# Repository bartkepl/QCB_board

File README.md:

# QCB (Quad Card Backplane)

Quad Card Backplane for 3U eurocards. Splits USB 2.0 and 10/100M Ethernet (plus RS485 and an ID EEPROM) out to 4 eurocards.

---

## Status: ready for prototype order

- Schematic and PCB routing are done (rev 0.1), production files generated.
- A full design review (schematic + PCB + EMC + SPICE) was completed on 2026-08-03 and re-checked since; see [Documentation](#documentation) below.
- Fiducials added (2 per side, hand assembly), Y2 load caps C41/C42 now included in the BOM, datasheets for IP175G, FE1.1s and UT8413A in [doc/datasheet/](doc/datasheet/).

Production outputs: [schematic PDF](prod/sch/QCB_board.pdf) · [PCB PDF](prod/pcb/QCB_board.pdf) · [interactive BOM](prod/ibom/QCB_board_ibom.html) · [gerbers](prod/QCB_board.zip)

---

## Architecture

The board is a backplane hub card built around two switching ICs, fanned out to 4 identical eurocard channels:

- **U1 (FE1.1s)** — 4-port USB 2.0 Hi-Speed hub, one port per channel.
- **IC1 (IP175G)** — 5-port 10/100 Ethernet switch. One port is broken out to an RJ45 (J3) via magnetics (H1102NL); the other 4 go to the channels.
- **4× channel (`con1.kicad_sch`, reused as CON1–CON4)** — each with its own USB D+/D-, Ethernet TX/RX pairs, RS485±, ESD protection, and an identification EEPROM (M24C02) on its own I2C bus.
- **`pwr.kicad_sch`** — power input (Molex Mini-Fit connector J6), polyfuse, ferrite bead, ESD protection. No on-board regulator — +3.3V/+5V/+12V are supplied by the backplane.
- Channels land on 4 backplane connectors (DIN41612 2×32, J7–J10).

4-layer PCB (F.Cu / In1.Cu / In2.Cu / B.Cu), 101.6 × 128.7 mm.

## Features

- 10/100 Ethernet switch with an external RJ45 port
- USB 2.0 Hi-Speed 4-port hub
- Per-channel RS485 and identification EEPROM
- 4× 3U 6TE eurocard, IEEE 1101.1-1998 format (128 × 30.1 mm)
- Powered entirely from the backplane (no on-board regulator)

## Repository structure

```
pcb/        KiCad project (schematic, PCB, jobsets, 3D packages, datasheets cache)
doc/        Design review report, TODO list and component datasheets (tracked, human-readable)
media/      Renders/photos used in this README
prod/       Generated production outputs (gerbers/zip, BOM, schematic & PCB PDFs)
analysis/   Raw output of automated design-review tooling (gitignored, regenerable)
```

## Documentation

- [doc/DESIGN_REVIEW_2026-08-03.md](doc/DESIGN_REVIEW_2026-08-03.md) — full schematic/PCB/EMC/SPICE design review
- [doc/TODO.md](doc/TODO.md) — outstanding items before the board can be ordered

## License and Contribution

[MIT License](/LICENSE)

Open to contributions in both software and hardware!

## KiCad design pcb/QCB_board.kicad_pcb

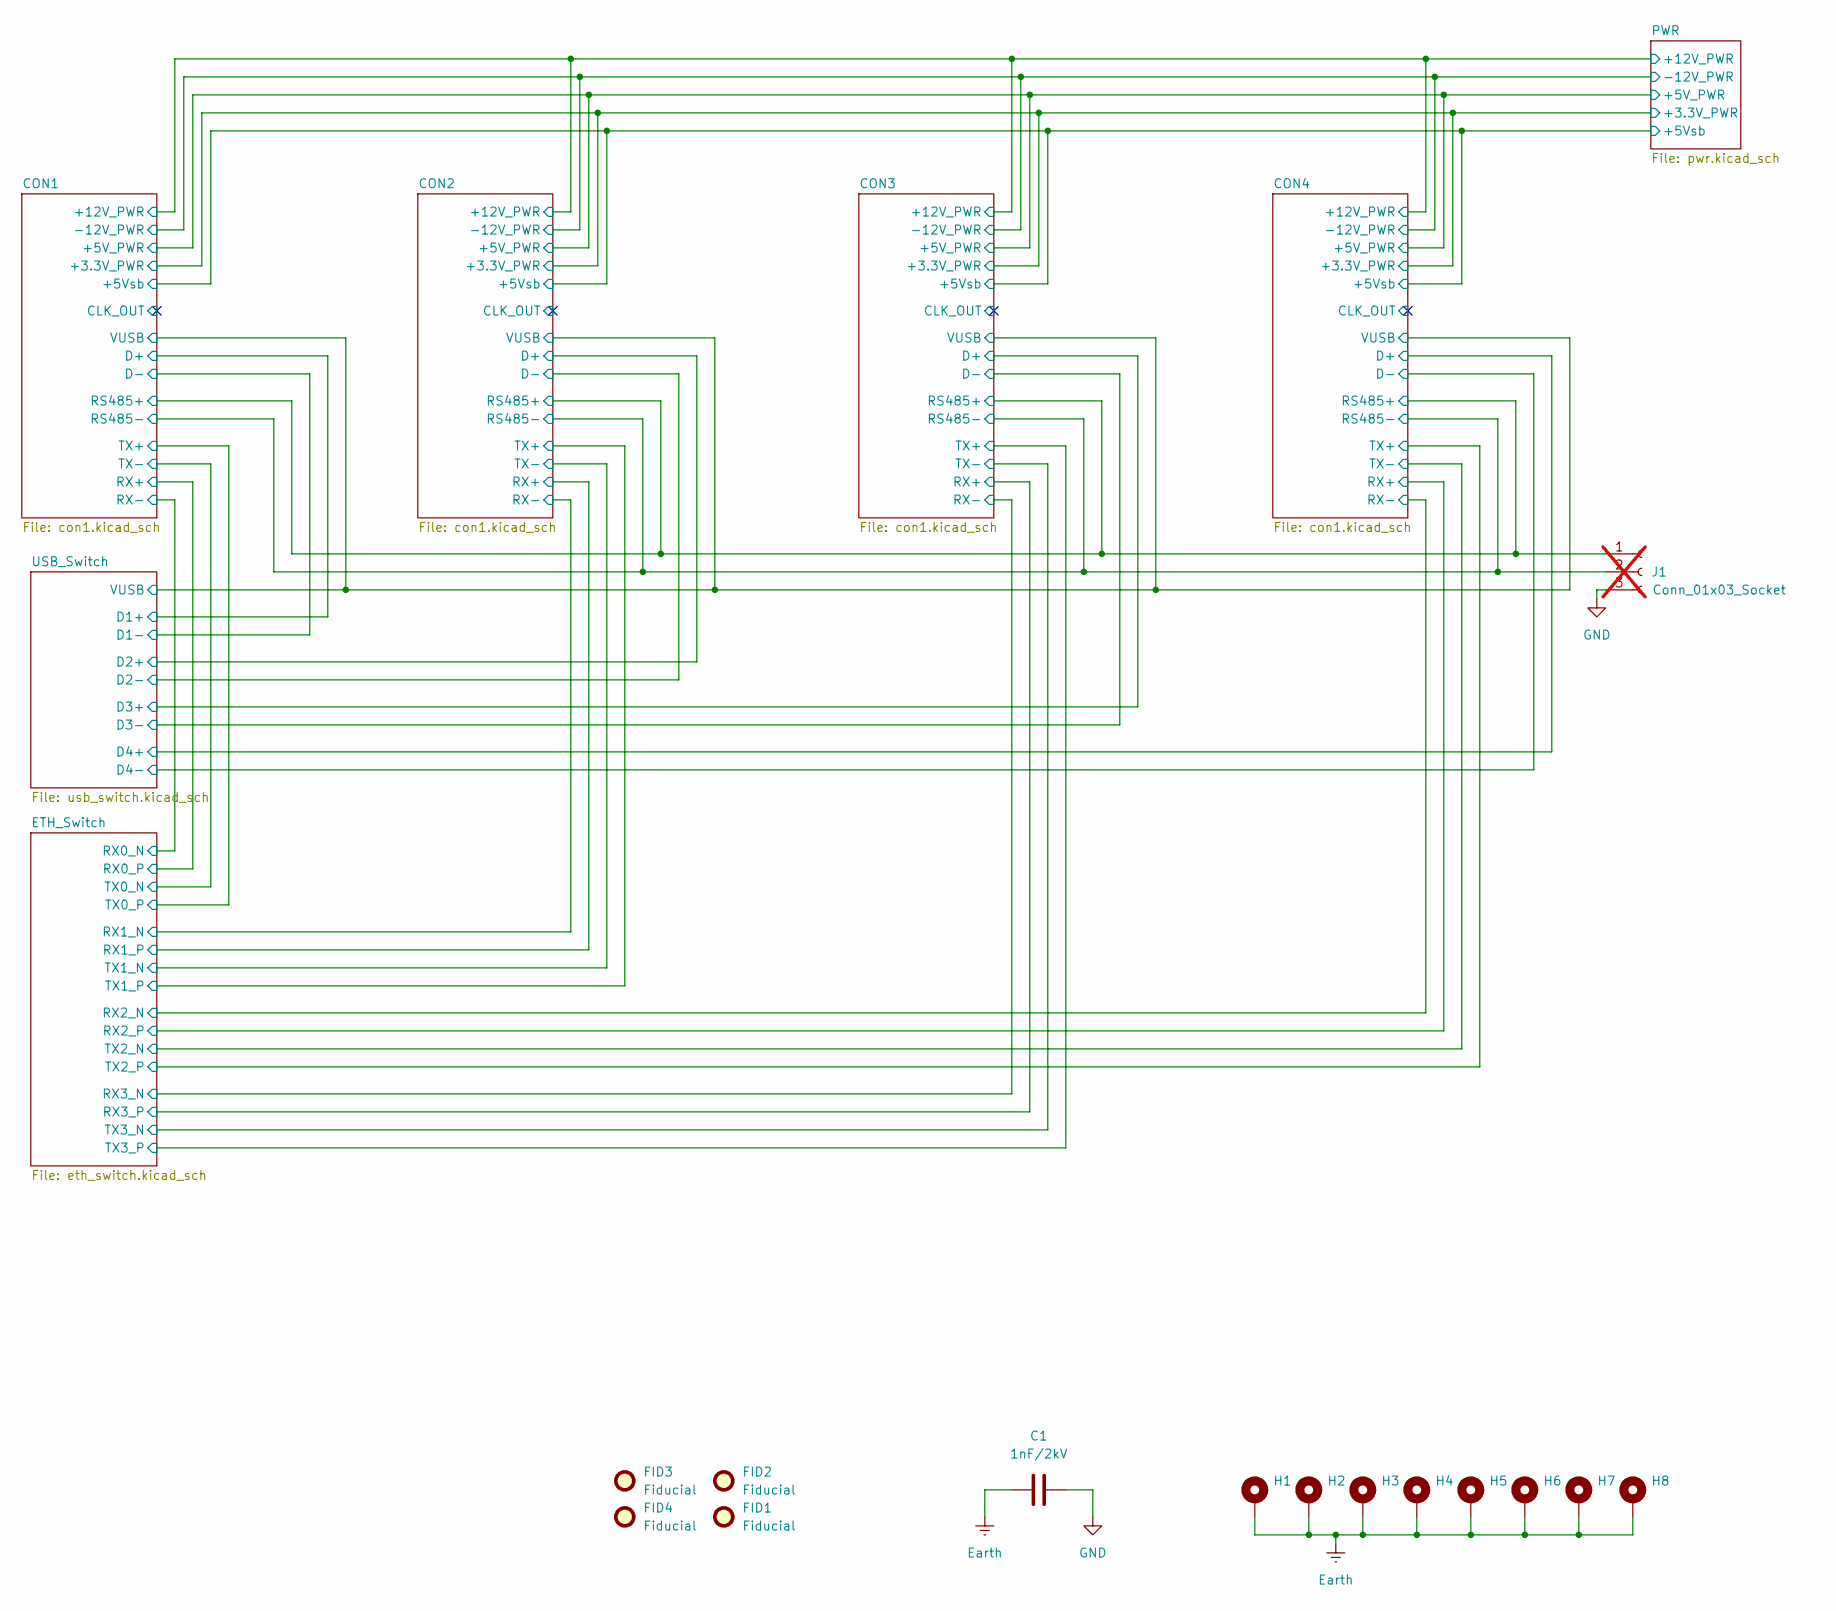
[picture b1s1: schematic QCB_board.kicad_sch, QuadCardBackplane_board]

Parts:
C1: 1nF/2kV; C_1206_3216Metric; MPN C1206X102K202T; LCSC C106012
FID1, FID2, FID3, FID4: Fiducial; Fiducial_0.5mm_Mask1mm
H1, H2, H3, H4, H5, H6, H7, H8: MountingHole_Pad; MountingHole_2.7mm_M2.5_DIN965_Pad
J1: Conn_01x03_Socket; JST_PH_B3B-PH-K_1x03_P2.00mm_Vertical; not fitted

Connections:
/CON1/RS485+: J1.1; also elsewhere on the board
/CON1/RS485-: J1.2; also elsewhere on the board
Earth: C1.1, H1.1 (1_1), H2.1 (1_1), H3.1 (1_1), H4.1 (1_1), H5.1 (1_1), H6.1 (1_1), H7.1 (1_1), H8.1 (1_1); also elsewhere on the board
GND: C1.2, J1.3; also elsewhere on the board

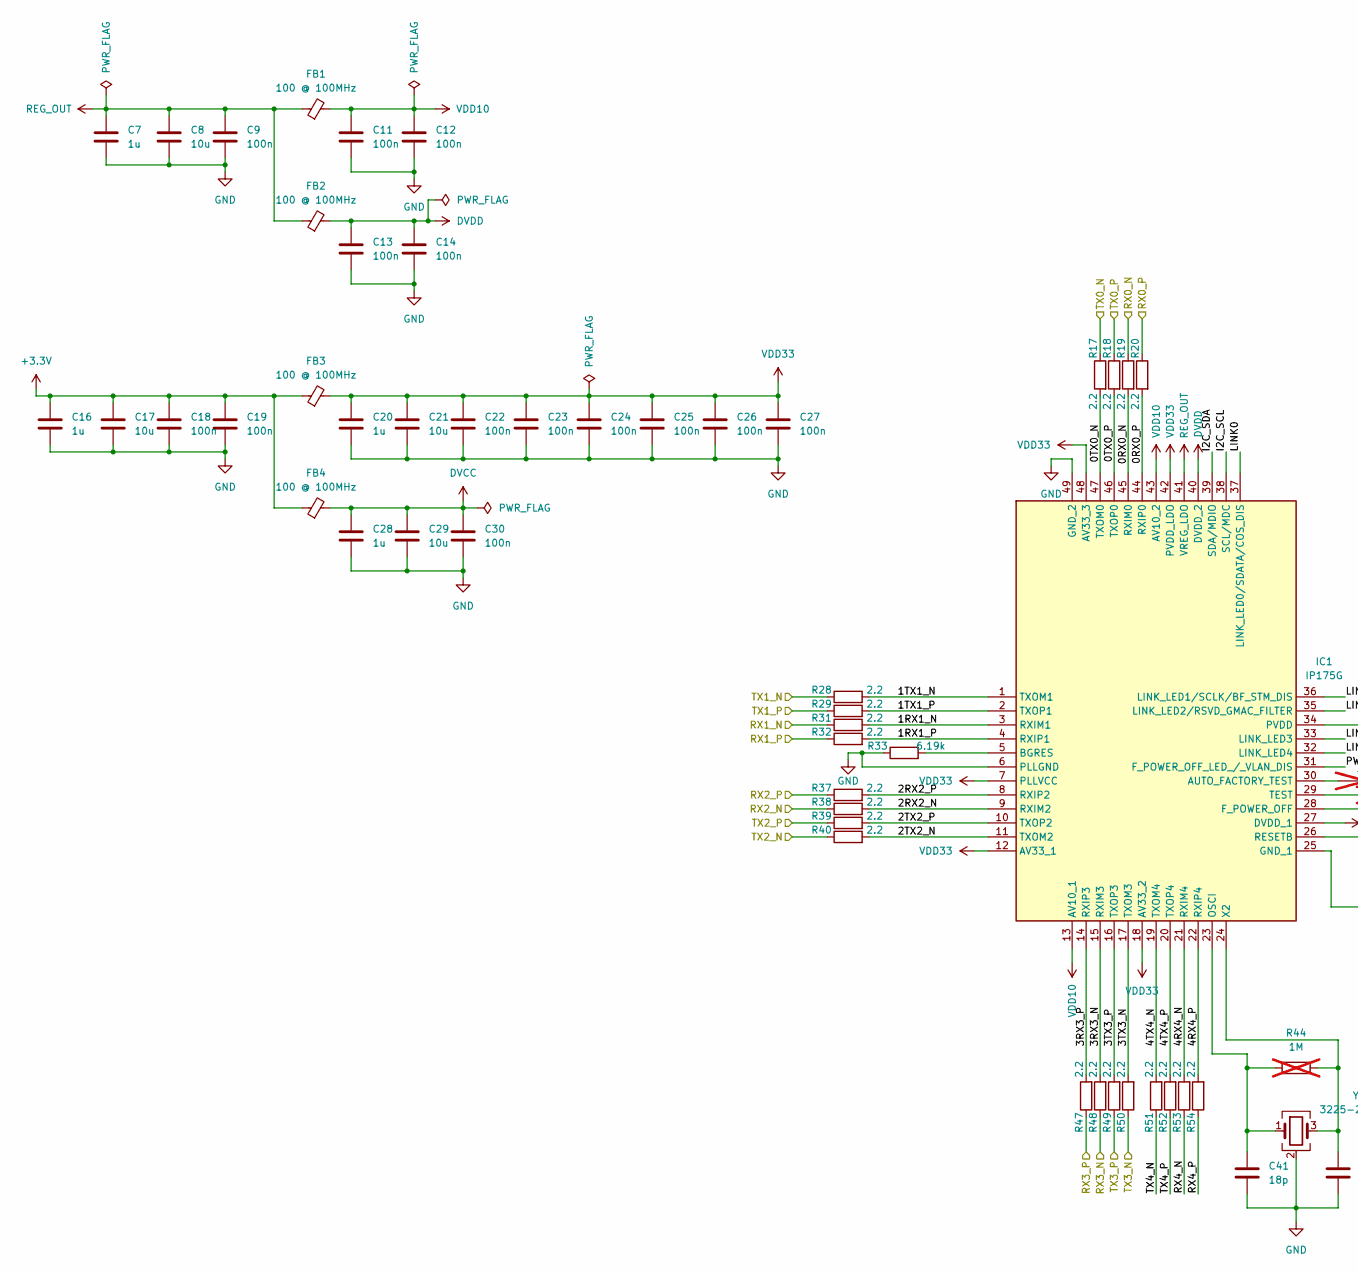
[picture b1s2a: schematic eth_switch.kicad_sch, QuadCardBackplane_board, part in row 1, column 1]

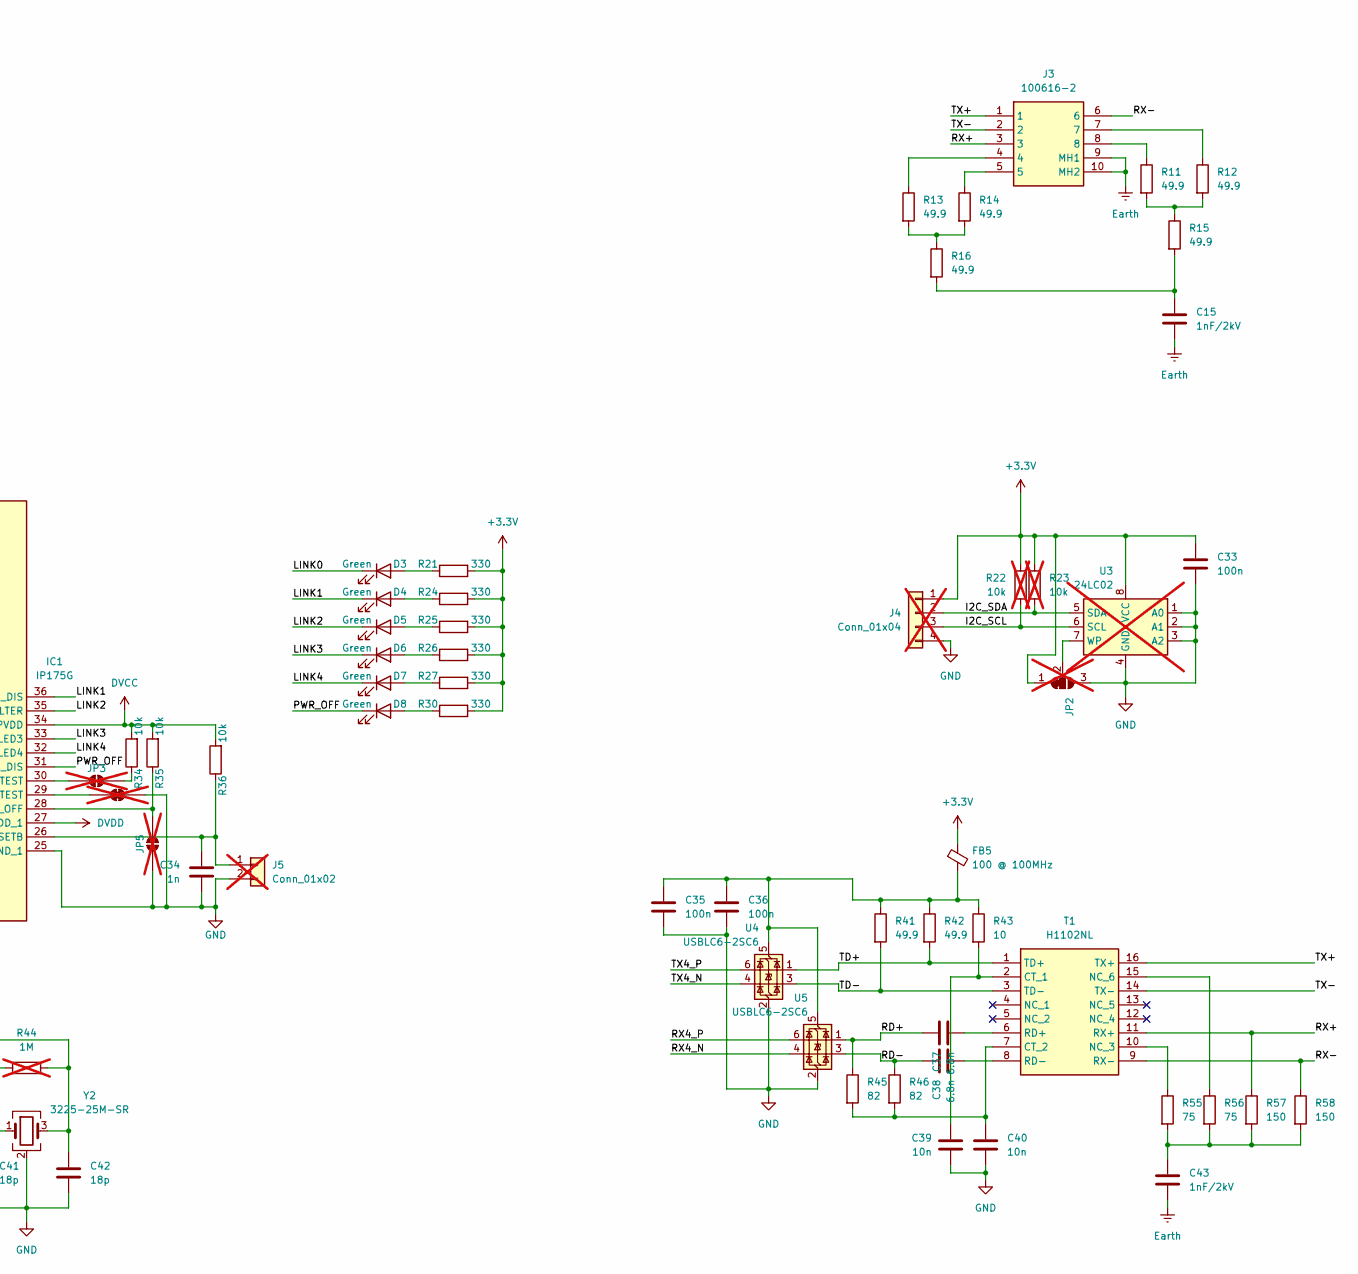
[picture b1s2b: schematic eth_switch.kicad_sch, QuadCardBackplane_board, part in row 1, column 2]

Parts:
C7, C16, C20, C28: 1u; C_0603_1608Metric; MPN 0603X105K500NT; LCSC C157684
C8, C17, C21, C29: 10u; C_1206_3216Metric; MPN CS3216X5R106K500NRI; LCSC C513774
C9, C11, C12, C13, C14, C18, C19, C22, C23, C24, C25, C26, C27, C30, C33, C35, C36: 100n; C_0603_1608Metric; MPN TCC0603X7R104K500CT; LCSC C282519
C15, C43: 1nF/2kV; C_1206_3216Metric; MPN C1206X102K202T; LCSC C106012
C34: 1n; C_0603_1608Metric; MPN CC0603JRNPO9BN102; LCSC C106246
C37, C38: 6.8n; C_0603_1608Metric; MPN C1608C0G1H682JT000N; LCSC C342851
C39, C40: 10n; C_0603_1608Metric; MPN GRM1885C1H103JA01J; LCSC C2215227
C41, C42: 18p; C_0402_1005Metric; MPN 0402CG180J500NT; LCSC C1549
D3, D4, D5, D6, D7, D8: Green; LED_0603_1608Metric; MPN N0G69S04
FB1, FB2, FB3, FB4, FB5: 100 @ 100MHz; L_0603_1608Metric_Pad1.05x0.95mm_HandSolder; MPN MH1608-101Y
IC1: IP175G; QFN40P600X600X90-49N-D; MPN IP175G; LCSC C80220
J3: 100616-2; 1006162; MPN 100616-2
J4: Conn_01x04; PinHeader_1x04_P1.00mm_Vertical; not fitted
J5: Conn_01x02; PinHeader_1x02_P1.00mm_Vertical; not fitted
JP2: SolderJumper_3_Bridged12; SolderJumper-3_P1.3mm_Bridged12_Pad1.0x1.5mm; not fitted
JP3, JP5: SolderJumper_2_Open; SolderJumper-2_P1.3mm_Open_RoundedPad1.0x1.5mm; not fitted
JP4: SolderJumper_2_Bridged; SolderJumper-2_P1.3mm_Bridged_RoundedPad1.0x1.5mm; not fitted
R11, R12, R13, R14, R15, R16, R41, R42: 49.9; R_0603_1608Metric; MPN SCR0603F49R9; LCSC C3016250
R17, R18, R19, R20, R28, R29, R31, R32, R37, R38, R39, R40, R47, R48, R49, R50, R51, R52, R53, R54: 2.2; R_0603_1608Metric; MPN FRC0603F2R20TS; LCSC C2907006
R21, R24, R25, R26, R27, R30: 330; R_0603_1608Metric; MPN SCR0603F330R; LCSC C3016255
R22, R23: 10k; R_0603_1608Metric; not fitted
R33: 6.19k; R_0603_1608Metric; MPN 0603WAF6191T5E; LCSC C25978
R34, R35, R36: 10k; R_0603_1608Metric; MPN RMS06FT1002; LCSC C209013
R43: 10; R_0603_1608Metric; MPN 0603WAF100JT5E; LCSC C22859
R44: 1M; R_0603_1608Metric; MPN 0603SAF1004T5E; not fitted
R45, R46: 82; R_0603_1608Metric; MPN FRC0603F82R0TS; LCSC C2907073
R55, R56: 75; R_0603_1608Metric; MPN 0603WAF750JT5E; LCSC C4275
R57, R58: 150; R_0603_1608Metric; MPN 0603WAF1500T5E; LCSC C22808
T1: H1102NL; SOIC127P940X597-16N; MPN H1102NLT; LCSC C20623173
U3: 24LC02; SOIC-8_3.9x4.9mm_P1.27mm; not fitted
U4, U5: USBLC6-2SC6; SOT-23-6_Handsoldering; MPN USBLC6-2SC6; LCSC C7519
Y2: 3225-25M-SR; Crystal_SMD_3225-4Pin_3.2x2.5mm; MPN 3225-25M-SR

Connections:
+3.3V: C16.1, C17.1, C18.1, C19.1, C33.1, FB3.1, FB4.1, FB5.1, J4.1, JP2.1 (A), R21.2, R22.2, R23.2, R24.2, R25.2, R26.2, R27.2, R30.2, U3.8 (VCC); also elsewhere on the board
/CON1/RX+: R20.1; also elsewhere on the board
/CON1/RX-: R19.1; also elsewhere on the board
/CON1/TX+: R18.1; also elsewhere on the board
/CON1/TX-: R17.1; also elsewhere on the board
/CON2/RX+: R32.1; also elsewhere on the board
/CON2/RX-: R31.1; also elsewhere on the board
/CON2/TX+: R29.1; also elsewhere on the board
/CON2/TX-: R28.1; also elsewhere on the board
/CON3/RX+: R47.1; also elsewhere on the board
/CON3/RX-: R48.1; also elsewhere on the board
/CON3/TX+: R49.1; also elsewhere on the board
/CON3/TX-: R50.1; also elsewhere on the board
/CON4/RX+: R37.1; also elsewhere on the board
/CON4/RX-: R38.1; also elsewhere on the board
/CON4/TX+: R39.1; also elsewhere on the board
/CON4/TX-: R40.1; also elsewhere on the board
/ETH_Switch/0RX0_N: IC1.45 (RXIM0), R19.2
/ETH_Switch/0RX0_P: IC1.44 (RXIP0), R20.2
/ETH_Switch/0TX0_N: IC1.47 (TXOM0), R17.2
/ETH_Switch/0TX0_P: IC1.46 (TXOP0), R18.2
/ETH_Switch/1RX1_N: IC1.3 (RXIM1), R31.2
/ETH_Switch/1RX1_P: IC1.4 (RXIP1), R32.2
/ETH_Switch/1TX1_N: IC1.1 (TXOM1), R28.2
/ETH_Switch/1TX1_P: IC1.2 (TXOP1), R29.2
/ETH_Switch/2RX2_N: IC1.9 (RXIM2), R38.2
/ETH_Switch/2RX2_P: IC1.8 (RXIP2), R37.2
/ETH_Switch/2TX2_N: IC1.11 (TXOM2), R40.2
/ETH_Switch/2TX2_P: IC1.10 (TXOP2), R39.2
/ETH_Switch/3RX3_N: IC1.15 (RXIM3), R48.2
/ETH_Switch/3RX3_P: IC1.14 (RXIP3), R47.2
/ETH_Switch/3TX3_N: IC1.17 (TXOM3), R50.2
/ETH_Switch/3TX3_P: IC1.16 (TXOP3), R49.2
/ETH_Switch/4RX4_N: IC1.21 (RXIM4), R53.2
/ETH_Switch/4RX4_P: IC1.22 (RXIP4), R54.2
/ETH_Switch/4TX4_N: IC1.19 (TXOM4), R51.2
/ETH_Switch/4TX4_P: IC1.20 (TXOP4), R52.2
/ETH_Switch/I2C_SCL: IC1.38 (SCL/MDC), J4.3, R22.1, U3.6 (SCL)
/ETH_Switch/I2C_SDA: IC1.39 (SDA/MDIO), J4.2, R23.1, U3.5 (SDA)
/ETH_Switch/LINK0: D3.1 (K), IC1.37 (LINK_LED0/SDATA/COS_DIS)
/ETH_Switch/LINK1: D4.1 (K), IC1.36 (LINK_LED1/SCLK/BF_STM_DIS)
/ETH_Switch/LINK2: D5.1 (K), IC1.35 (LINK_LED2/RSVD_GMAC_FILTER)
/ETH_Switch/LINK3: D6.1 (K), IC1.33 (LINK_LED3)
/ETH_Switch/LINK4: D7.1 (K), IC1.32 (LINK_LED4)
/ETH_Switch/PWR_OFF: D8.1 (K), IC1.31 (F_POWER_OFF_LED_/_VLAN_DIS)
/ETH_Switch/RD+: C37.2, R45.1, U5.1 (I/O1)
/ETH_Switch/RD-: C38.2, R46.1, U5.3 (I/O2)
/ETH_Switch/RX4_N: R53.1, U5.4 (I/O2)
/ETH_Switch/RX4_P: R54.1, U5.6 (I/O1)
/ETH_Switch/RX+: J3.3, R57.1, T1.11 (RX+)
/ETH_Switch/RX-: J3.6, R58.1, T1.9 (RX-)
/ETH_Switch/TD+: R42.2, T1.1 (TD+), U4.1 (I/O1)
/ETH_Switch/TD-: R41.2, T1.3 (TD-), U4.3 (I/O2)
/ETH_Switch/TX4_N: R51.1, U4.4 (I/O2)
/ETH_Switch/TX4_P: R52.1, U4.6 (I/O1)
/ETH_Switch/TX+: J3.1, T1.16 (TX+)
/ETH_Switch/TX-: J3.2, T1.14 (TX-)
DVCC: C28.1, C29.1, C30.1, FB4.2, IC1.34 (PVDD), R34.2, R35.2, R36.2
DVDD: C13.1, C14.1, FB2.2, IC1.27 (DVDD_1), IC1.40 (DVDD_2)
Earth: C15.2, C43.2, J3.9 (MH1), J3.10 (MH2); also elsewhere on the board
GND: C7.2, C8.2, C9.2, C11.2, C12.2, C13.2, C14.2, C16.2, C17.2, C18.2, C19.2, C20.2, C21.2, C22.2, C23.2, C24.2, C25.2, C26.2, C27.2, C28.2, C29.2, C30.2, C33.2, C34.1, C35.2, C36.2, C39.1, C40.2, C41.2, C42.2, IC1.6 (PLLGND), IC1.25 (GND_1), IC1.49 (GND_2), J4.4, J5.2, JP2.3 (B), JP4.2 (B), JP5.1 (A), R33.1, U3.1 (A0), U3.2 (A1), U3.3 (A2), U3.4 (GND), U4.2 (GND), U5.2 (GND), Y2.2 (G), Y2.4 (G); also elsewhere on the board
unnamed: C15.1, R15.2, R16.2
unnamed: C43.1, R55.2, R56.2, R57.2, R58.2
unnamed: D3.2 (A), R21.1
unnamed: D4.2 (A), R24.1
unnamed: D5.2 (A), R25.1
unnamed: D6.2 (A), R26.1
unnamed: D7.2 (A), R27.1
unnamed: D8.2 (A), R30.1
unnamed: IC1.30 (AUTO_FACTORY_TEST), JP3.1 (A)
unnamed: IC1.5 (BGRES), R33.2
unnamed: IC1.28 (F_POWER_OFF), JP5.2 (B), R35.1
unnamed: C41.1, IC1.23 (OSCI), R44.1, Y2.1
unnamed: C34.2, IC1.26 (RESETB), J5.1, R36.1
unnamed: IC1.29 (TEST), JP4.1 (A)
unnamed: C42.1, IC1.24 (X2), R44.2, Y2.3
unnamed: J3.4, R13.1
unnamed: J3.5, R14.1
unnamed: J3.7, R12.1
unnamed: J3.8, R11.1
unnamed: JP2.2 (C), U3.7 (WP)
unnamed: JP3.2 (B), R34.1
unnamed: R11.2, R12.2, R15.1
unnamed: R13.2, R14.2, R16.1
unnamed: C39.2, R43.2, T1.2 (CT_1)
unnamed: C40.1, R45.2, R46.2, T1.7 (CT_2)
unnamed: R55.1, T1.10 (NC_3)
unnamed: R56.1, T1.15 (NC_6)
unnamed: C37.1, T1.6 (RD+)
unnamed: C38.1, T1.8 (RD-)
unnamed: C35.1, C36.1, FB5.2, R41.1, R42.1, R43.1, U4.5 (VBUS), U5.5 (VBUS)
REG_OUT: C7.1, C8.1, C9.1, FB1.1, FB2.1, IC1.41 (VREG_LDO)
VDD10: C11.1, C12.1, FB1.2, IC1.13 (AV10_1), IC1.43 (AV10_2)
VDD33: C20.1, C21.1, C22.1, C23.1, C24.1, C25.1, C26.1, C27.1, FB3.2, IC1.7 (PLLVCC), IC1.12 (AV33_1), IC1.18 (AV33_2), IC1.42 (PVDD_LDO), IC1.48 (AV33_3)

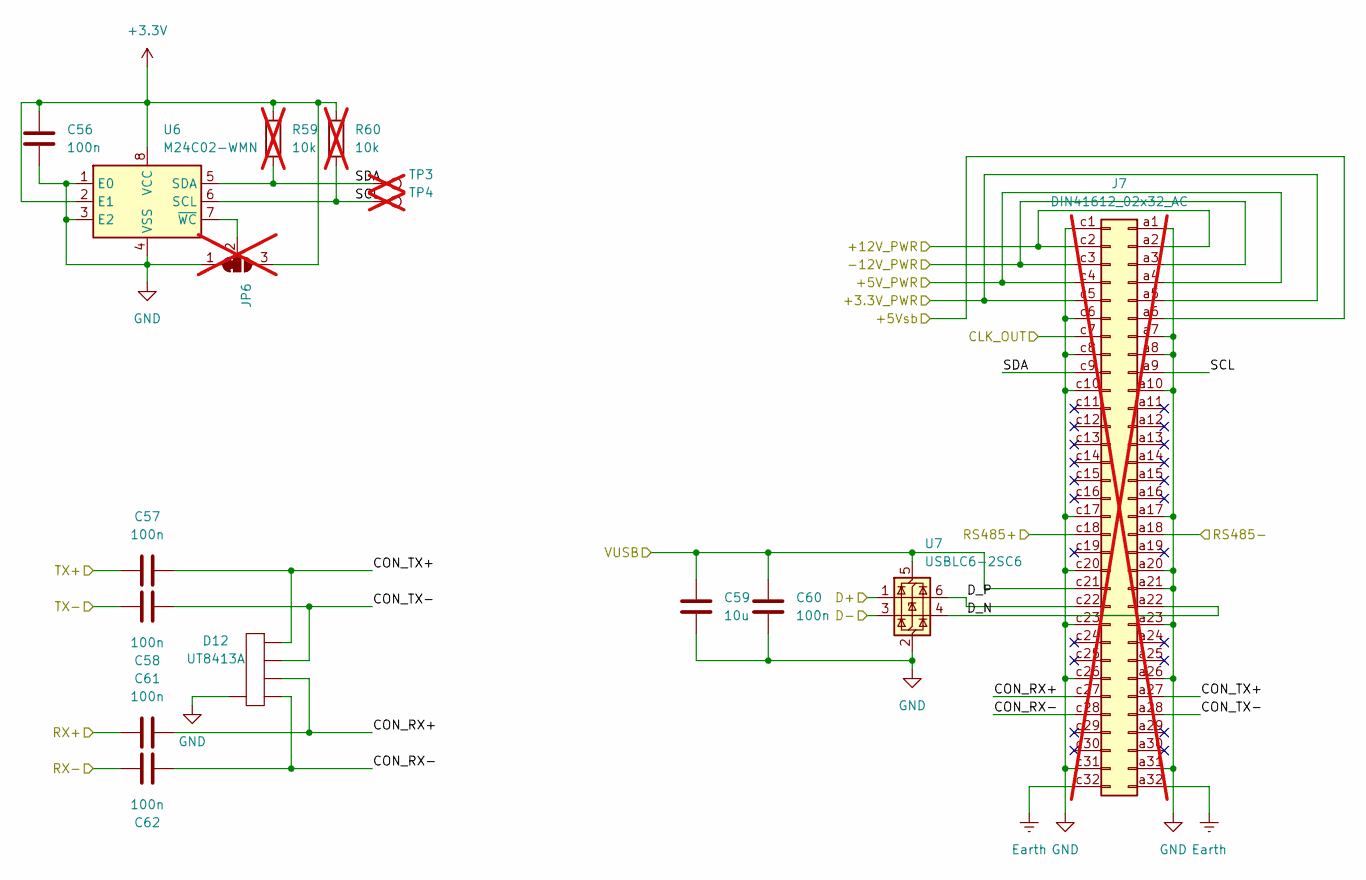
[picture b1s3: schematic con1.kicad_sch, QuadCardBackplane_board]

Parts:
C56, C60: 100n; C_0603_1608Metric; MPN TCC0603X7R104K500CT; LCSC C282519
C57, C58, C61, C62: 100n; C_0805_2012Metric; MPN C2012X7T2E104K125AA; Mouser 810-C2012X7T2E104KAA
C59: 10u; C_1206_3216Metric; MPN CS3216X5R106K500NRI; LCSC C513774
D12: UT8413A; Diodes_UDFN-10_1x2.5mm_P0.5mm; MPN UT8413A
J7: DIN41612_02x32_AC; DIN41612_C_2x32_Female_Vertical_THT; not fitted
JP6: SolderJumper_3_Bridged12; SolderJumper-3_P1.3mm_Bridged12_Pad1.0x1.5mm; not fitted
R59, R60: 10k; R_0603_1608Metric; not fitted
TP3, TP4: TestPoint; TestPoint_Pad_D1.0mm; not fitted
U6: M24C02-WMN; SOIC-8_3.9x4.9mm_P1.27mm; MPN M24C02-WMN6TP; Mouser 511-M24C02-WMN6TP
U7: USBLC6-2SC6; SOT-23-6_Handsoldering; MPN USBLC6-2SC6; LCSC C7519

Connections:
+3.3V: C56.2, JP6.3 (B), R59.2, R60.2, U6.2 (E1), U6.8 (VCC); also elsewhere on the board
/CON1/+3.3V_PWR: J7.a5, J7.c5; also elsewhere on the board
/CON1/+5V_PWR: J7.a4, J7.c4; also elsewhere on the board
/CON1/+5Vsb: J7.a6; also elsewhere on the board
/CON1/+12V_PWR: J7.a2, J7.c2; also elsewhere on the board
/CON1/-12V_PWR: J7.a3, J7.c3; also elsewhere on the board
/CON1/CLK_OUT: J7.c7
/CON1/CON_RX+: C61.2, D12.2, D12.9, J7.c27
/CON1/CON_RX-: C62.2, D12.1, D12.10, J7.c28
/CON1/CON_TX+: C57.2, D12.5, D12.6, J7.a27
/CON1/CON_TX-: C58.2, D12.4, D12.7, J7.a28
/CON1/D+: U7.1 (I/O1); also elsewhere on the board
/CON1/D-: U7.3 (I/O2); also elsewhere on the board
/CON1/D_N: J7.a22, U7.4 (I/O2)
/CON1/D_P: J7.c22, U7.6 (I/O1)
/CON1/RS485+: J7.c18; also elsewhere on the board
/CON1/RS485-: J7.a18; also elsewhere on the board
/CON1/RX+: C61.1; also elsewhere on the board
/CON1/RX-: C62.1; also elsewhere on the board
/CON1/SCL: J7.a9, R60.1, TP4.1 (1_1), U6.6 (SCL)
/CON1/SDA: J7.c9, R59.1, TP3.1 (1_1), U6.5 (SDA)
/CON1/TX+: C57.1; also elsewhere on the board
/CON1/TX-: C58.1; also elsewhere on the board
/CON1/VUSB: C59.1, C60.2, J7.c21, U7.5 (VBUS); also elsewhere on the board
Earth: J7.a32, J7.c32; also elsewhere on the board
GND: C56.1, C59.2, C60.1, D12.3, D12.8, J7.a1, J7.a7, J7.a8, J7.a10, J7.a17, J7.a20, J7.a21, J7.a23, J7.a26, J7.a31, J7.c1, J7.c6, J7.c8, J7.c10, J7.c17, J7.c20, J7.c23, J7.c26, J7.c31, JP6.1 (A), U6.1 (E0), U6.3 (E2), U6.4 (VSS), U7.2 (GND); also elsewhere on the board
unnamed: JP6.2 (C), U6.7 (~WC)

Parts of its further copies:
C63, C67, C70, C74, C77, C81: 100n; C_0603_1608Metric; MPN TCC0603X7R104K500CT; LCSC C282519
C64, C65, C68, C69, C71, C72, C75, C76, C78, C79, C82, C83: 100n; C_0805_2012Metric; MPN C2012X7T2E104K125AA; Mouser 810-C2012X7T2E104KAA
C66, C73, C80: 10u; C_1206_3216Metric; MPN CS3216X5R106K500NRI; LCSC C513774
D13, D14, D15: UT8413A; Diodes_UDFN-10_1x2.5mm_P0.5mm; MPN UT8413A
J8, J9, J10: DIN41612_02x32_AC; DIN41612_C_2x32_Female_Vertical_THT; not fitted
JP7, JP8, JP9: SolderJumper_3_Bridged12; SolderJumper-3_P1.3mm_Bridged12_Pad1.0x1.5mm; not fitted
R61, R62, R63, R64, R65, R66: 10k; R_0603_1608Metric; not fitted
TP5, TP6, TP7, TP8, TP9, TP10: TestPoint; TestPoint_Pad_D1.0mm; not fitted
U8, U10, U12: M24C02-WMN; SOIC-8_3.9x4.9mm_P1.27mm; MPN M24C02-WMN6TP; Mouser 511-M24C02-WMN6TP
U9, U11, U13: USBLC6-2SC6; SOT-23-6_Handsoldering; MPN USBLC6-2SC6; LCSC C7519

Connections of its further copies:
+3.3V: C63.2, C70.2, C77.2, JP7.3 (B), JP8.3 (B), JP9.3 (B), R61.2, R62.2, R63.2, R64.2, R65.2, R66.2, U8.2 (E1), U8.8 (VCC), U10.2 (E1), U10.8 (VCC), U12.2 (E1), U12.8 (VCC); also elsewhere on the board
/CON1/+3.3V_PWR: J8.a5, J8.c5, J9.a5, J9.c5, J10.a5, J10.c5; also elsewhere on the board
/CON1/+5V_PWR: J8.a4, J8.c4, J9.a4, J9.c4, J10.a4, J10.c4; also elsewhere on the board
/CON1/+5Vsb: J8.a6, J9.a6, J10.a6; also elsewhere on the board
/CON1/+12V_PWR: J8.a2, J8.c2, J9.a2, J9.c2, J10.a2, J10.c2; also elsewhere on the board
/CON1/-12V_PWR: J8.a3, J8.c3, J9.a3, J9.c3, J10.a3, J10.c3; also elsewhere on the board
/CON1/RS485+: J8.c18, J9.c18, J10.c18; also elsewhere on the board
/CON1/RS485-: J8.a18, J9.a18, J10.a18; also elsewhere on the board
/CON1/VUSB: C66.1, C67.2, C73.1, C74.2, C80.1, C81.2, J8.c21, J9.c21, J10.c21, U9.5 (VBUS), U11.5 (VBUS), U13.5 (VBUS); also elsewhere on the board
/CON2/CLK_OUT: J8.c7
/CON2/CON_RX+: C68.2, D13.2, D13.9, J8.c27
/CON2/CON_RX-: C69.2, D13.1, D13.10, J8.c28
/CON2/CON_TX+: C64.2, D13.5, D13.6, J8.a27
/CON2/CON_TX-: C65.2, D13.4, D13.7, J8.a28
/CON2/D+: U9.1 (I/O1); also elsewhere on the board
/CON2/D-: U9.3 (I/O2); also elsewhere on the board
/CON2/D_N: J8.a22, U9.4 (I/O2)
/CON2/D_P: J8.c22, U9.6 (I/O1)
/CON2/RX+: C68.1; also elsewhere on the board
/CON2/RX-: C69.1; also elsewhere on the board
/CON2/SCL: J8.a9, R62.1, TP6.1 (1_1), U8.6 (SCL)
/CON2/SDA: J8.c9, R61.1, TP5.1 (1_1), U8.5 (SDA)
/CON2/TX+: C64.1; also elsewhere on the board
/CON2/TX-: C65.1; also elsewhere on the board
/CON3/CLK_OUT: J9.c7
/CON3/CON_RX+: C75.2, D14.2, D14.9, J9.c27
/CON3/CON_RX-: C76.2, D14.1, D14.10, J9.c28
/CON3/CON_TX+: C71.2, D14.5, D14.6, J9.a27
/CON3/CON_TX-: C72.2, D14.4, D14.7, J9.a28
/CON3/D+: U11.1 (I/O1); also elsewhere on the board
/CON3/D-: U11.3 (I/O2); also elsewhere on the board
/CON3/D_N: J9.a22, U11.4 (I/O2)
/CON3/D_P: J9.c22, U11.6 (I/O1)
/CON3/RX+: C75.1; also elsewhere on the board
/CON3/RX-: C76.1; also elsewhere on the board
/CON3/SCL: J9.a9, R64.1, TP8.1 (1_1), U10.6 (SCL)
/CON3/SDA: J9.c9, R63.1, TP7.1 (1_1), U10.5 (SDA)
/CON3/TX+: C71.1; also elsewhere on the board
/CON3/TX-: C72.1; also elsewhere on the board
/CON4/CLK_OUT: J10.c7
/CON4/CON_RX+: C82.2, D15.2, D15.9, J10.c27
/CON4/CON_RX-: C83.2, D15.1, D15.10, J10.c28
/CON4/CON_TX+: C78.2, D15.5, D15.6, J10.a27
/CON4/CON_TX-: C79.2, D15.4, D15.7, J10.a28
/CON4/D+: U13.1 (I/O1); also elsewhere on the board
/CON4/D-: U13.3 (I/O2); also elsewhere on the board
/CON4/D_N: J10.a22, U13.4 (I/O2)
/CON4/D_P: J10.c22, U13.6 (I/O1)
/CON4/RX+: C82.1; also elsewhere on the board
/CON4/RX-: C83.1; also elsewhere on the board
/CON4/SCL: J10.a9, R66.1, TP10.1 (1_1), U12.6 (SCL)
/CON4/SDA: J10.c9, R65.1, TP9.1 (1_1), U12.5 (SDA)
/CON4/TX+: C78.1; also elsewhere on the board
/CON4/TX-: C79.1; also elsewhere on the board
Earth: J8.a32, J8.c32, J9.a32, J9.c32, J10.a32, J10.c32; also elsewhere on the board
GND: C63.1, C66.2, C67.1, C70.1, C73.2, C74.1, C77.1, C80.2, C81.1, D13.3, D13.8, D14.3, D14.8, D15.3, D15.8, J8.a1, J8.a7, J8.a8, J8.a10, J8.a17, J8.a20, J8.a21, J8.a23, J8.a26, J8.a31, J8.c1, J8.c6, J8.c8, J8.c10, J8.c17, J8.c20, J8.c23, J8.c26, J8.c31, J9.a1, J9.a7, J9.a8, J9.a10, J9.a17, J9.a20, J9.a21, J9.a23, J9.a26, J9.a31, J9.c1, J9.c6, J9.c8, J9.c10, J9.c17, J9.c20, J9.c23, J9.c26, J9.c31, J10.a1, J10.a7, J10.a8, J10.a10, J10.a17, J10.a20, J10.a21, J10.a23, J10.a26, J10.a31, J10.c1, J10.c6, J10.c8, J10.c10, J10.c17, J10.c20, J10.c23, J10.c26, J10.c31, JP7.1 (A), JP8.1 (A), JP9.1 (A), U8.1 (E0), U8.3 (E2), U8.4 (VSS), U9.2 (GND), U10.1 (E0), U10.3 (E2), U10.4 (VSS), U11.2 (GND), U12.1 (E0), U12.3 (E2), U12.4 (VSS), U13.2 (GND); also elsewhere on the board
unnamed: JP7.2 (C), U8.7 (~WC)
unnamed: JP8.2 (C), U10.7 (~WC)
unnamed: JP9.2 (C), U12.7 (~WC)

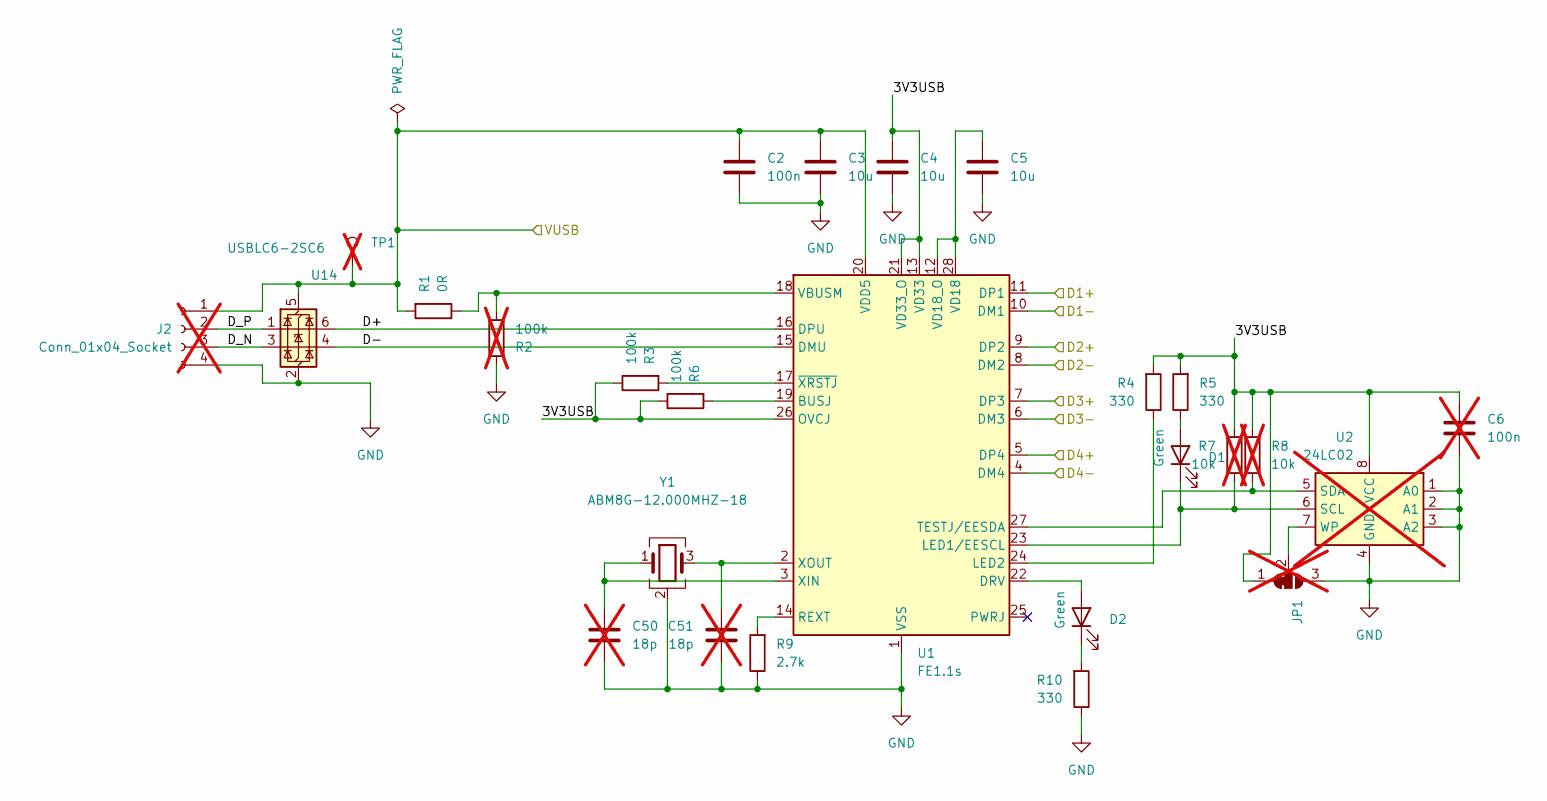
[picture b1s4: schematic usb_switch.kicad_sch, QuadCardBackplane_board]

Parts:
C2: 100n; C_0603_1608Metric; MPN TCC0603X7R104K500CT; LCSC C282519
C3, C4, C5: 10u; C_1206_3216Metric; MPN CS3216X5R106K500NRI; LCSC C513774
C6: 100n; C_0603_1608Metric; not fitted
C50, C51: 18p; C_0402_1005Metric; not fitted
D1, D2: Green; LED_0603_1608Metric; MPN N0G69S04
J2: Conn_01x04_Socket; JST_PH_B4B-PH-K_1x04_P2.00mm_Vertical; not fitted
JP1: SolderJumper_3_Bridged12; SolderJumper-3_P1.3mm_Bridged12_Pad1.0x1.5mm; not fitted
R1: 0R; R_0603_1608Metric; MPN 0603WAJ0000T5E; LCSC C15402
R2: 100k; R_0603_1608Metric; not fitted
R3, R6: 100k; R_0603_1608Metric; MPN RC0603FR-07100KL; LCSC C14675
R4, R5, R10: 330; R_0603_1608Metric; MPN SCR0603F330R; LCSC C3016255
R7, R8: 10k; R_0603_1608Metric; not fitted
R9: 2.7k; R_0603_1608Metric; MPN CQ03WAF2701T5E; LCSC C966658
TP1: TestPoint; TestPoint_Pad_D1.0mm; not fitted
U1: FE1.1s; SSOP-28_3.9x9.9mm_P0.635mm; MPN FE1.1S-BSOP28BCN; LCSC C9359
U2: 24LC02; SOIC-8_3.9x4.9mm_P1.27mm; not fitted
U14: USBLC6-2SC6; SOT-23-6_Handsoldering; MPN USBLC6-2SC6; LCSC C7519
Y1: ABM8G-12.000MHZ-18; Crystal_SMD_Abracon_ABM8G-4Pin_3.2x2.5mm; MPN ABM8G-12.000MHZ-18-D2Y-T

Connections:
/CON1/D+: U1.11 (DP1); also elsewhere on the board
/CON1/D-: U1.10 (DM1); also elsewhere on the board
/CON1/VUSB: C2.1, C3.1, J2.1, R1.2, TP1.1 (1_1), U1.20 (VDD5), U14.5 (VBUS); also elsewhere on the board
/CON2/D+: U1.9 (DP2); also elsewhere on the board
/CON2/D-: U1.8 (DM2); also elsewhere on the board
/CON3/D+: U1.7 (DP3); also elsewhere on the board
/CON3/D-: U1.6 (DM3); also elsewhere on the board
/CON4/D+: U1.5 (DP4); also elsewhere on the board
/CON4/D-: U1.4 (DM4); also elsewhere on the board
/USB_Switch/3V3USB: C4.1, C6.1, JP1.1 (A), R3.1, R4.2, R5.2, R6.1, R7.2, R8.2, U1.13 (VD33), U1.21 (VD33_O), U1.26 (OVCJ), U2.8 (VCC)
/USB_Switch/D+: U1.16 (DPU), U14.6 (I/O1)
/USB_Switch/D-: U1.15 (DMU), U14.4 (I/O2)
/USB_Switch/D_N: J2.3, U14.3 (I/O2)
/USB_Switch/D_P: J2.2, U14.1 (I/O1)
GND: C2.2, C3.2, C4.2, C5.2, C6.2, C50.2, C51.2, J2.4, JP1.3 (B), R2.2, R9.1, R10.1, U1.1 (VSS), U2.1 (A0), U2.2 (A1), U2.3 (A2), U2.4 (GND), U14.2 (GND), Y1.2 (G), Y1.4 (G); also elsewhere on the board
unnamed: D1.2 (A), R5.1
unnamed: D1.1 (K), R7.1, U1.23 (LED1/EESCL), U2.6 (SCL)
unnamed: D2.2 (A), U1.22 (DRV)
unnamed: D2.1 (K), R10.2
unnamed: JP1.2 (C), U2.7 (WP)
unnamed: R6.2, U1.19 (BUSJ)
unnamed: R4.1, U1.24 (LED2)
unnamed: R9.2, U1.14 (REXT)
unnamed: R8.1, U1.27 (TESTJ/EESDA), U2.5 (SDA)
unnamed: R1.1, R2.1, U1.18 (VBUSM)
unnamed: C5.1, U1.12 (VD18_O), U1.28 (VD18)
unnamed: C50.1, U1.3 (XIN), Y1.1
unnamed: C51.1, U1.2 (XOUT), Y1.3
unnamed: R3.2, U1.17 (~XRSTJ)

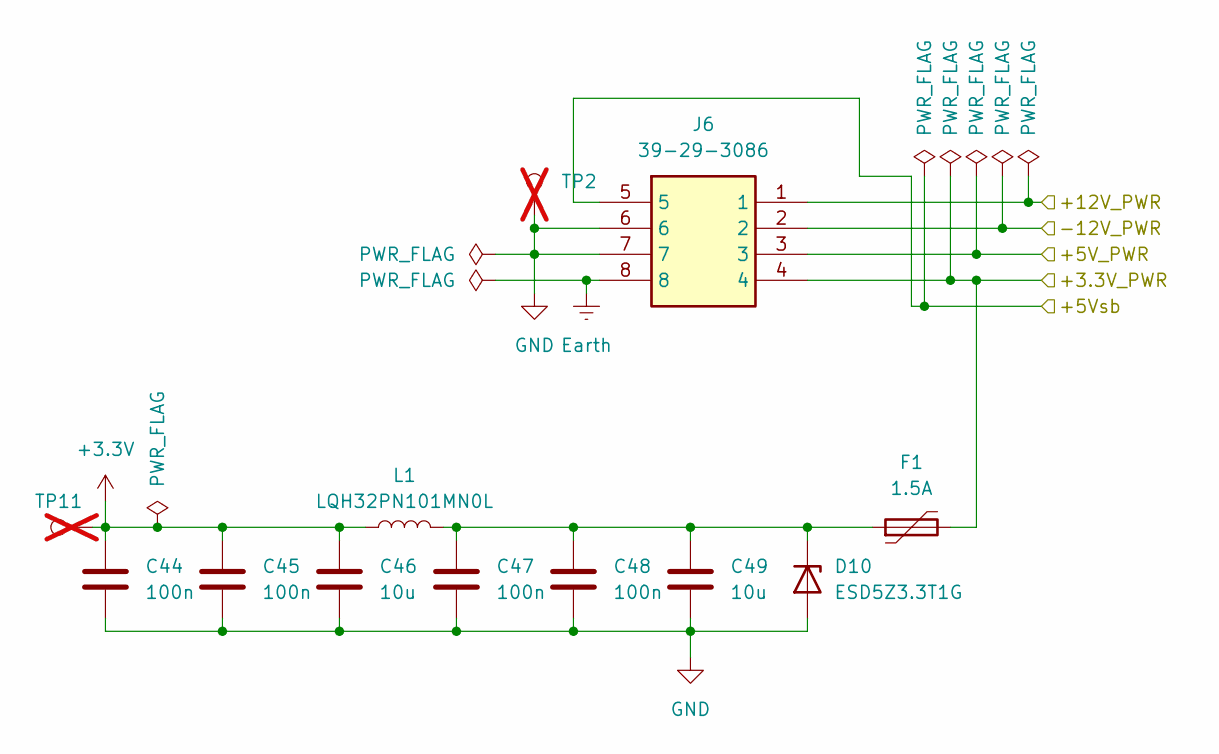
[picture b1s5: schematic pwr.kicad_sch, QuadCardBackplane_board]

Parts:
C44, C45, C47, C48: 100n; C_0603_1608Metric; MPN TCC0603X7R104K500CT; LCSC C282519
C46, C49: 10u; C_1206_3216Metric; MPN CS3216X5R106K500NRI; LCSC C513774
D10: ESD5Z3.3T1G; D_SOD-523; MPN ESD5Z3.3T5G; Mouser 863-ESD5Z3.3T5G
F1: 1.5A; Fuse_1206_3216Metric_Pad1.42x1.75mm_HandSolder; MPN 1206L150/12NR; LCSC C19078714
J6: 39-29-3086; Molex_Mini-Fit_Jr_5566-08A_2x04_P4.20mm_Vertical; MPN 39-29-3086
L1: LQH32PN101MN0L; L_1210_3225Metric; MPN LQH32PN101MN0L
TP2, TP11: TestPoint; TestPoint_Pad_D1.0mm; not fitted

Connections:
+3.3V: C44.1, C45.1, C46.1, L1.1, TP11.1 (1_1); also elsewhere on the board
/CON1/+3.3V_PWR: F1.2, J6.4; also elsewhere on the board
/CON1/+5V_PWR: J6.3; also elsewhere on the board
/CON1/+5Vsb: J6.5; also elsewhere on the board
/CON1/+12V_PWR: J6.1; also elsewhere on the board
/CON1/-12V_PWR: J6.2; also elsewhere on the board
Earth: J6.8; also elsewhere on the board
GND: C44.2, C45.2, C46.2, C47.2, C48.2, C49.2, D10.2 (A), J6.6, J6.7, TP2.1 (1_1); also elsewhere on the board
unnamed: C47.1, C48.1, C49.1, D10.1 (K), F1.1, L1.2
